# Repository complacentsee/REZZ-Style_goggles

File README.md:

View this project on [CADLAB.io](https://cadlab.io/project/1121). 

# REZZ-Style_goggles

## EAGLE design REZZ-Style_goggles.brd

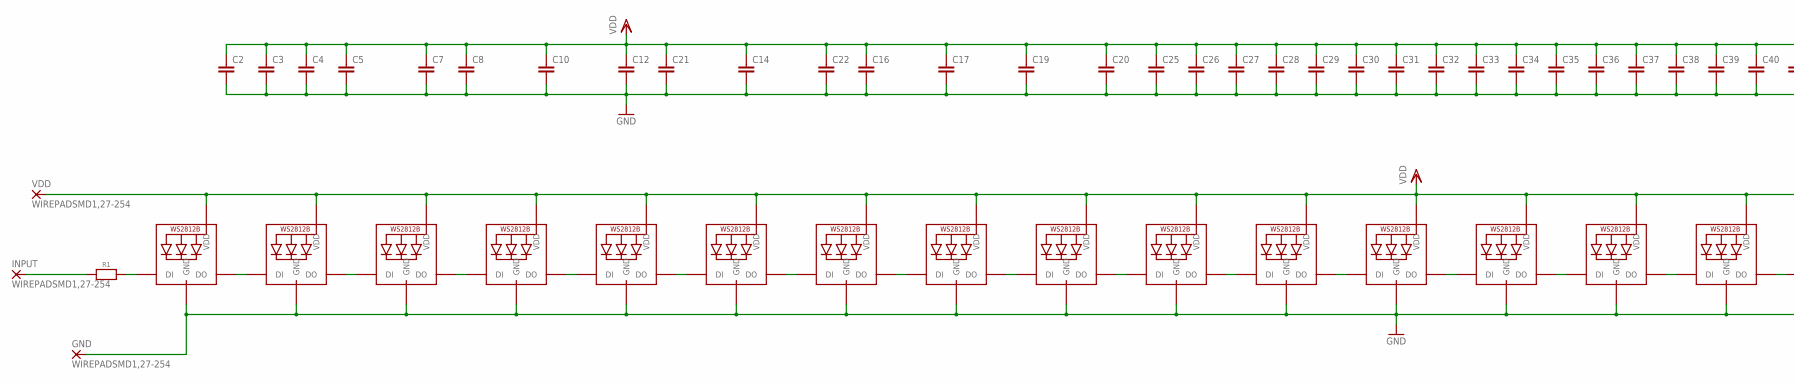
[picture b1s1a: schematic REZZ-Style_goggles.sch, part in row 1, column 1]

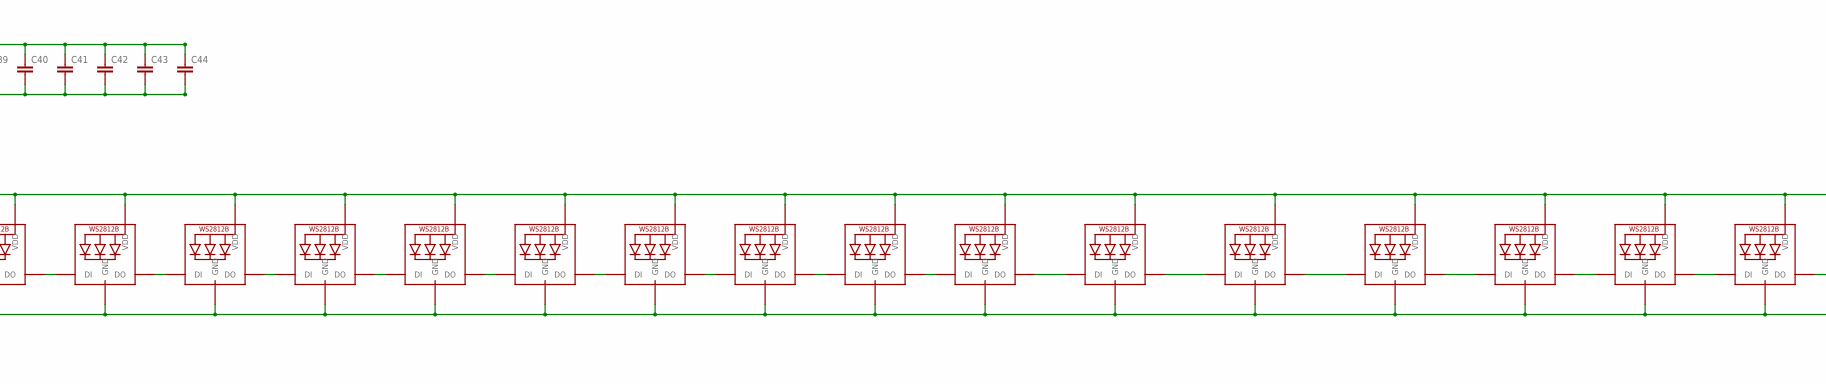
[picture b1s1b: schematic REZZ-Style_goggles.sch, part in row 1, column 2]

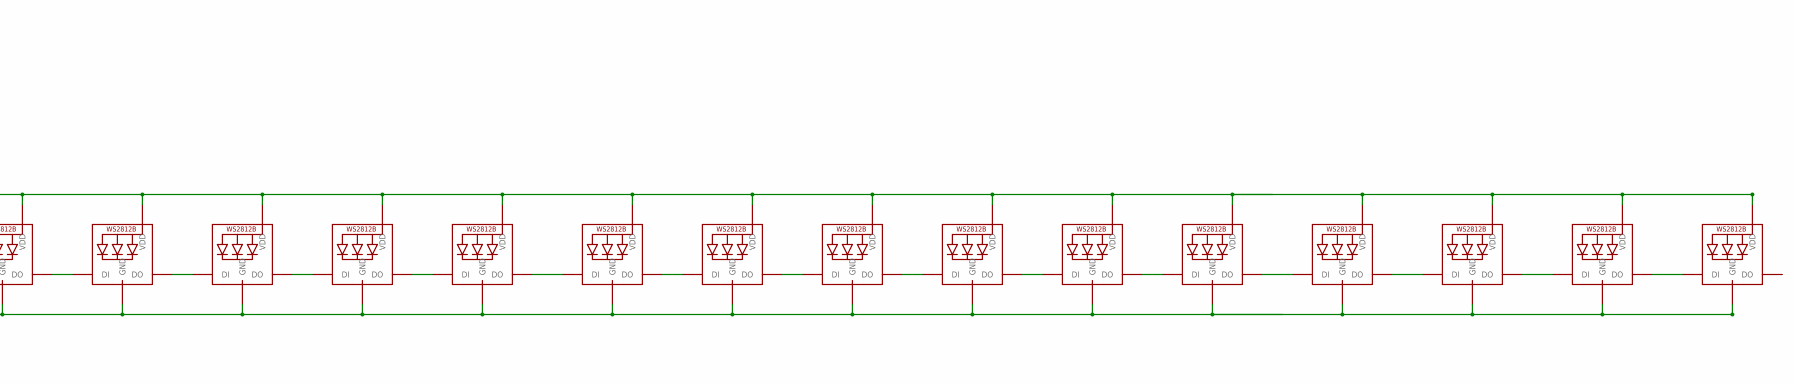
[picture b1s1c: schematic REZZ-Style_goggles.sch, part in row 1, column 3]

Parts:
C2, C3, C4, C5, C7, C8, C10, C12, C14, C16, C17, C19, C20, C21, C22, C25, C26, C27, C28, C29, C30, C31, C32, C33, C34, C35, C36, C37, C38, C39, C40, C41, C42, C43, C44: C-EUC0603; C0603
GND: WIREPADSMD1,27-254; SMD1,27-2,54
INPUT: WIREPADSMD1,27-254; SMD1,27-2,54
LED1, LED2, LED3, LED4, LED5, LED6, LED7, LED8, LED9, LED10, LED11, LED12, LED13, LED14, LED15, LED16, LED17, LED18, LED19, LED20, LED21, LED22, LED23, LED24, LED25, LED26, LED27, LED28, LED29, LED30, LED31, LED32, LED33, LED34, LED35, LED36, LED37, LED38, LED39, LED40, LED41, LED42, LED43, LED44: WS2812B3535; LED3535
R1: RESISTOR_0603_NOOUT; 0603-NO
VDD: WIREPADSMD1,27-254; SMD1,27-2,54

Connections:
GND: C2.2, C3.2, C4.2, C5.2, C7.2, C8.2, C10.2, C12.2, C14.2, C16.2, C17.2, C19.2, C20.2, C21.2, C22.2, C25.2, C26.2, C27.2, C28.2, C29.2, C30.2, C31.2, C32.2, C33.2, C34.2, C35.2, C36.2, C37.2, C38.2, C39.2, C40.2, C41.2, C42.2, C43.2, C44.2, GND.1, LED1.4 (GND), LED2.4 (GND), LED3.4 (GND), LED4.4 (GND), LED5.4 (GND), LED6.4 (GND), LED7.4 (GND), LED8.4 (GND), LED9.4 (GND), LED10.4 (GND), LED11.4 (GND), LED12.4 (GND), LED13.4 (GND), LED14.4 (GND), LED15.4 (GND), LED16.4 (GND), LED17.4 (GND), LED18.4 (GND), LED19.4 (GND), LED20.4 (GND), LED21.4 (GND), LED22.4 (GND), LED23.4 (GND), LED24.4 (GND), LED25.4 (GND), LED26.4 (GND), LED27.4 (GND), LED28.4 (GND), LED29.4 (GND), LED30.4 (GND), LED31.4 (GND), LED32.4 (GND), LED33.4 (GND), LED34.4 (GND), LED35.4 (GND), LED36.4 (GND), LED37.4 (GND), LED38.4 (GND), LED39.4 (GND), LED40.4 (GND), LED41.4 (GND), LED42.4 (GND), LED43.4 (GND), LED44.4 (GND)
unnamed: LED1.3 (DO), LED2.1 (DI)
unnamed: LED2.3 (DO), LED3.1 (DI)
unnamed: LED3.3 (DO), LED4.1 (DI)
unnamed: LED4.3 (DO), LED5.1 (DI)
unnamed: LED5.3 (DO), LED6.1 (DI)
unnamed: LED6.3 (DO), LED7.1 (DI)
unnamed: LED7.3 (DO), LED8.1 (DI)
unnamed: LED8.3 (DO), LED9.1 (DI)
unnamed: LED9.3 (DO), LED10.1 (DI)
unnamed: LED10.3 (DO), LED11.1 (DI)
unnamed: LED11.3 (DO), LED12.1 (DI)
unnamed: LED12.3 (DO), LED13.1 (DI)
unnamed: LED13.3 (DO), LED14.1 (DI)
unnamed: LED14.3 (DO), LED15.1 (DI)
unnamed: LED15.3 (DO), LED16.1 (DI)
unnamed: LED16.3 (DO), LED17.1 (DI)
unnamed: LED17.3 (DO), LED18.1 (DI)
unnamed: LED18.3 (DO), LED19.1 (DI)
unnamed: LED19.3 (DO), LED20.1 (DI)
unnamed: LED20.3 (DO), LED21.1 (DI)
unnamed: LED21.3 (DO), LED22.1 (DI)
unnamed: LED22.3 (DO), LED23.1 (DI)
unnamed: LED23.3 (DO), LED24.1 (DI)
unnamed: LED24.3 (DO), LED25.1 (DI)
unnamed: LED1.1 (DI), R1.2
unnamed: INPUT.1, R1.1
unnamed: LED25.3 (DO), LED26.1 (DI)
unnamed: LED26.3 (DO), LED27.1 (DI)
unnamed: LED27.3 (DO), LED28.1 (DI)
unnamed: LED28.3 (DO), LED29.1 (DI)
unnamed: LED29.3 (DO), LED30.1 (DI)
unnamed: LED30.3 (DO), LED31.1 (DI)
unnamed: LED31.3 (DO), LED32.1 (DI)
unnamed: LED32.3 (DO), LED33.1 (DI)
unnamed: LED33.3 (DO), LED34.1 (DI)
unnamed: LED34.3 (DO), LED35.1 (DI)
unnamed: LED35.3 (DO), LED36.1 (DI)
unnamed: LED36.3 (DO), LED37.1 (DI)
unnamed: LED37.3 (DO), LED38.1 (DI)
unnamed: LED38.3 (DO), LED39.1 (DI)
unnamed: LED39.3 (DO), LED40.1 (DI)
unnamed: LED40.3 (DO), LED41.1 (DI)
unnamed: LED41.3 (DO), LED42.1 (DI)
unnamed: LED42.3 (DO), LED43.1 (DI)
unnamed: LED43.3 (DO), LED44.1 (DI)
VDD: C2.1, C3.1, C4.1, C5.1, C7.1, C8.1, C10.1, C12.1, C14.1, C16.1, C17.1, C19.1, C20.1, C21.1, C22.1, C25.1, C26.1, C27.1, C28.1, C29.1, C30.1, C31.1, C32.1, C33.1, C34.1, C35.1, C36.1, C37.1, C38.1, C39.1, C40.1, C41.1, C42.1, C43.1, C44.1, LED1.2 (VDD), LED2.2 (VDD), LED3.2 (VDD), LED4.2 (VDD), LED5.2 (VDD), LED6.2 (VDD), LED7.2 (VDD), LED8.2 (VDD), LED9.2 (VDD), LED10.2 (VDD), LED11.2 (VDD), LED12.2 (VDD), LED13.2 (VDD), LED14.2 (VDD), LED15.2 (VDD), LED16.2 (VDD), LED17.2 (VDD), LED18.2 (VDD), LED19.2 (VDD), LED20.2 (VDD), LED21.2 (VDD), LED22.2 (VDD), LED23.2 (VDD), LED24.2 (VDD), LED25.2 (VDD), LED26.2 (VDD), LED27.2 (VDD), LED28.2 (VDD), LED29.2 (VDD), LED30.2 (VDD), LED31.2 (VDD), LED32.2 (VDD), LED33.2 (VDD), LED34.2 (VDD), LED35.2 (VDD), LED36.2 (VDD), LED37.2 (VDD), LED38.2 (VDD), LED39.2 (VDD), LED40.2 (VDD), LED41.2 (VDD), LED42.2 (VDD), LED43.2 (VDD), LED44.2 (VDD), VDD.1

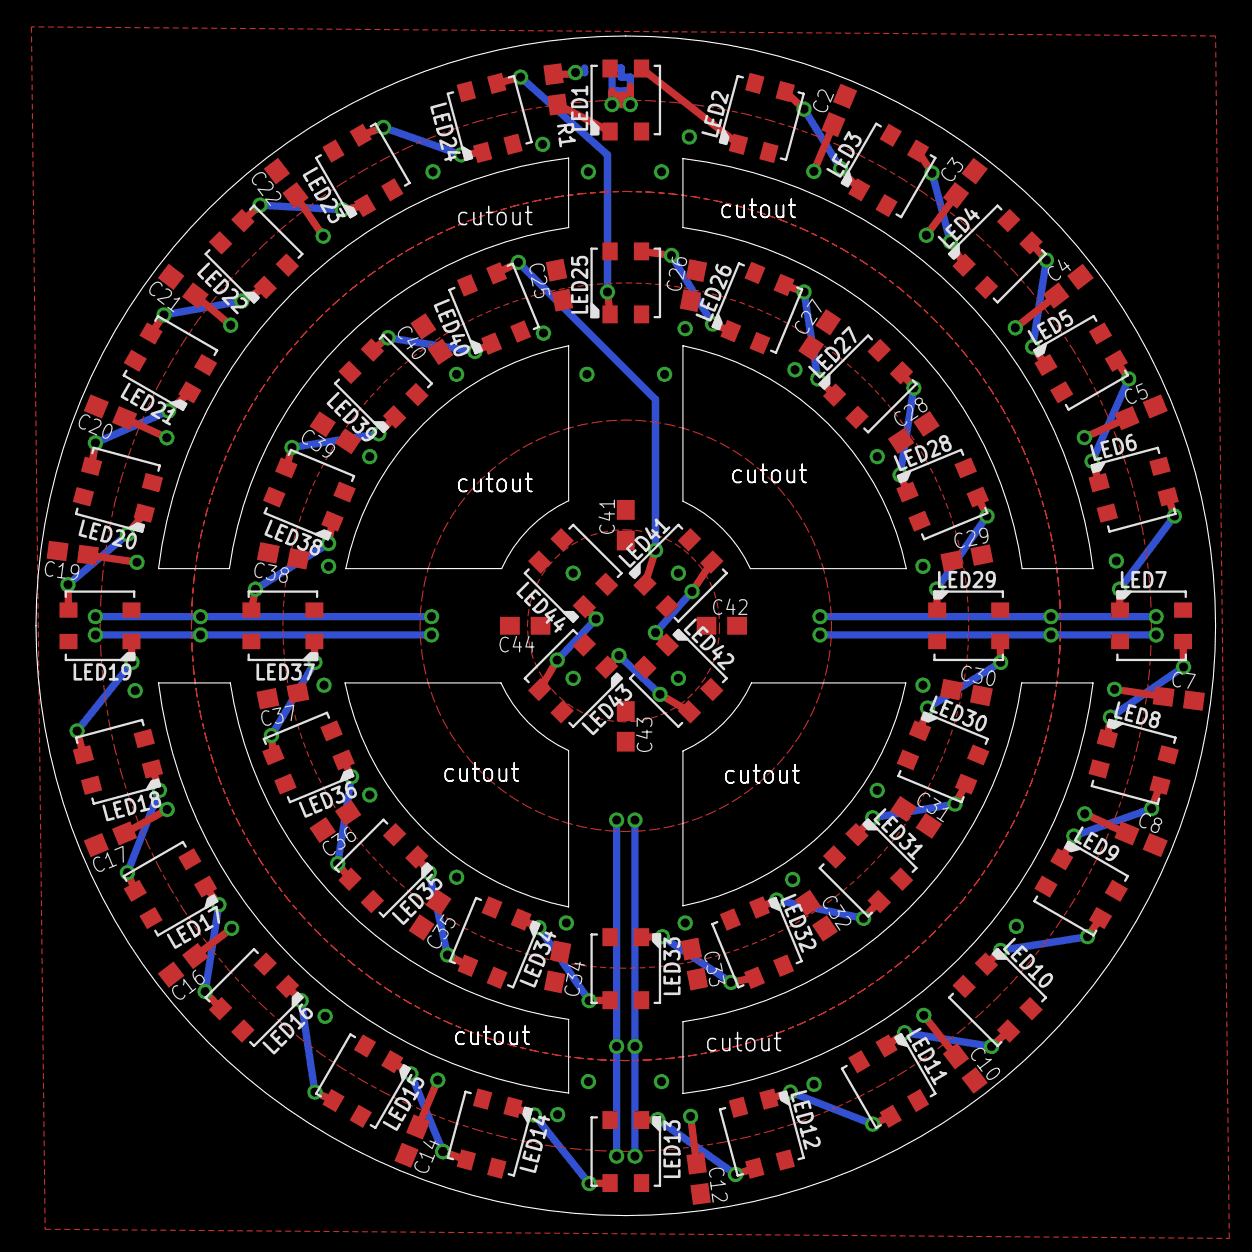
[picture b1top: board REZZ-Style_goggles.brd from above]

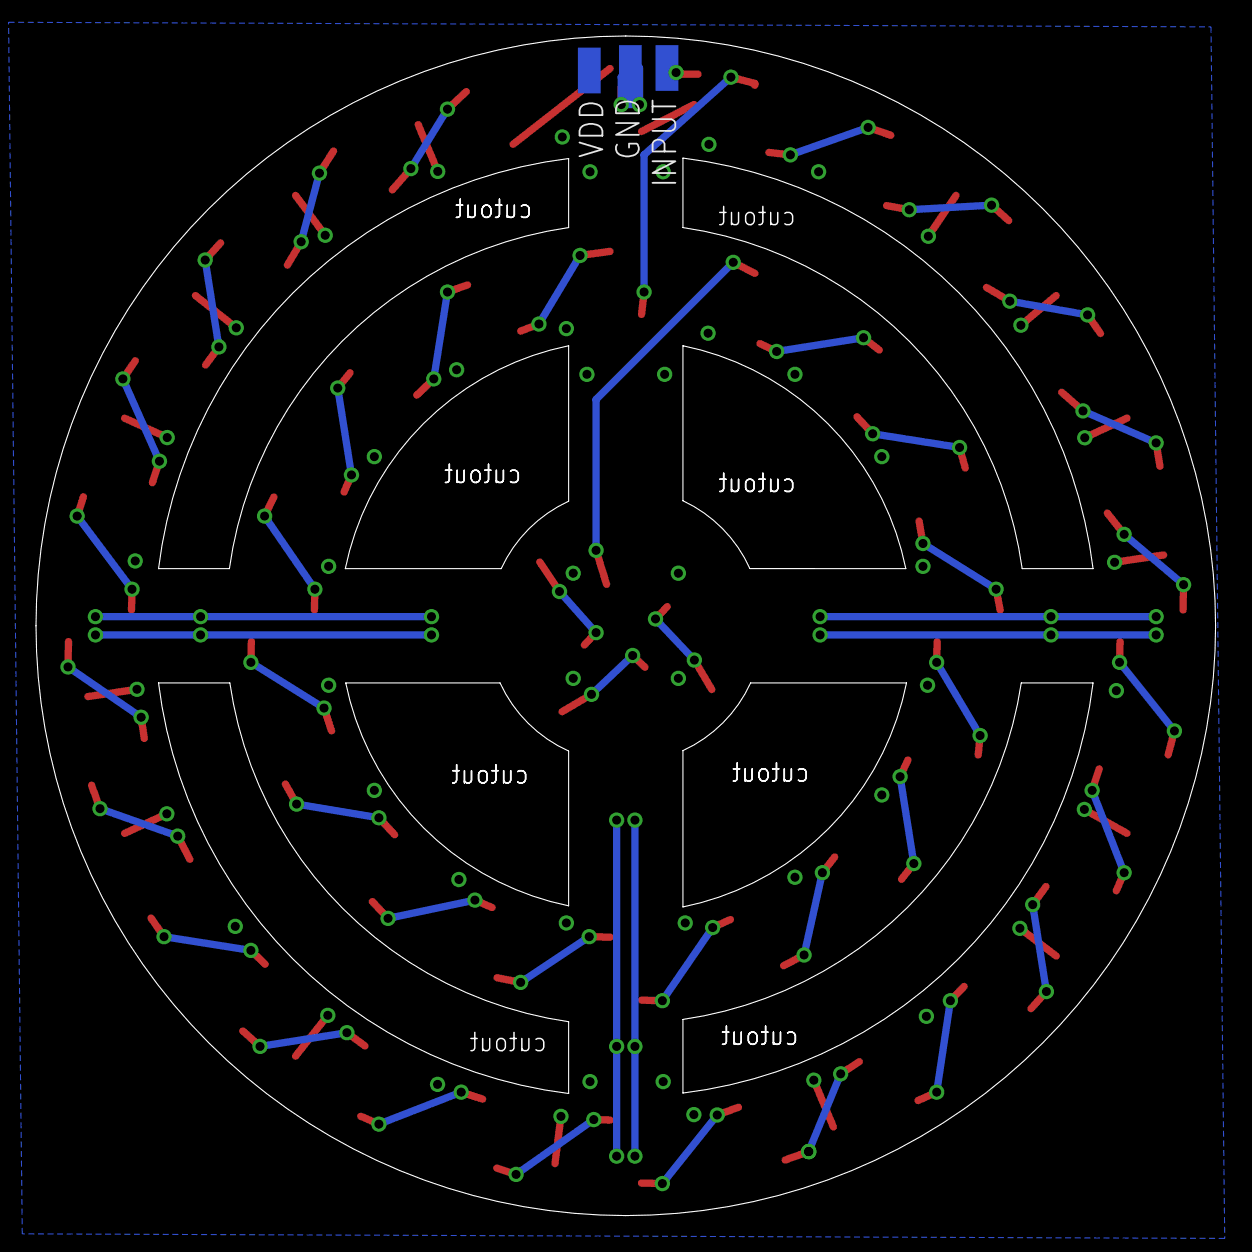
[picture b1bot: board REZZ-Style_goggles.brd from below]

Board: 2 copper layers, 65.5 x 65.5 mm, 83 parts (3 on the bottom side), 47 nets.

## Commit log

2016-12-12 second ring completed
2016-12-12 trace adjustments
2016-12-14 inner ring completed
2016-12-14 Sample layer images added
2016-12-14 revised placements to improve pours
2016-12-17 misc minor revs
2016-12-18 revised pads, adjusted silk screen
2016-12-18 Updated - First production order
2016-12-18 added gerbers
2018-06-02 Backlink to CADLAB.io has been added.

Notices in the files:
parts and their libraries:
microbuilder: This work is placed in the public domain, and may be freely used for commercial and non-commercial work with the following conditions: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
